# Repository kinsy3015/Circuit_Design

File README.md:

# Circuit_Design

# Internal Oscillatation eqi Circuit

# Wheatstone Current to Voltage

# POWER MANAGEMENT BASIC

# RF class C ( LC Resonant Circuit )

# NE555 안정 / 비안정, 스위칭 레귤레이터, Voltage Divider, Adder(Opamp)

# 다이오드 브릿지 +, -

# ADC IC, MUX/DEMUX

# Gerber

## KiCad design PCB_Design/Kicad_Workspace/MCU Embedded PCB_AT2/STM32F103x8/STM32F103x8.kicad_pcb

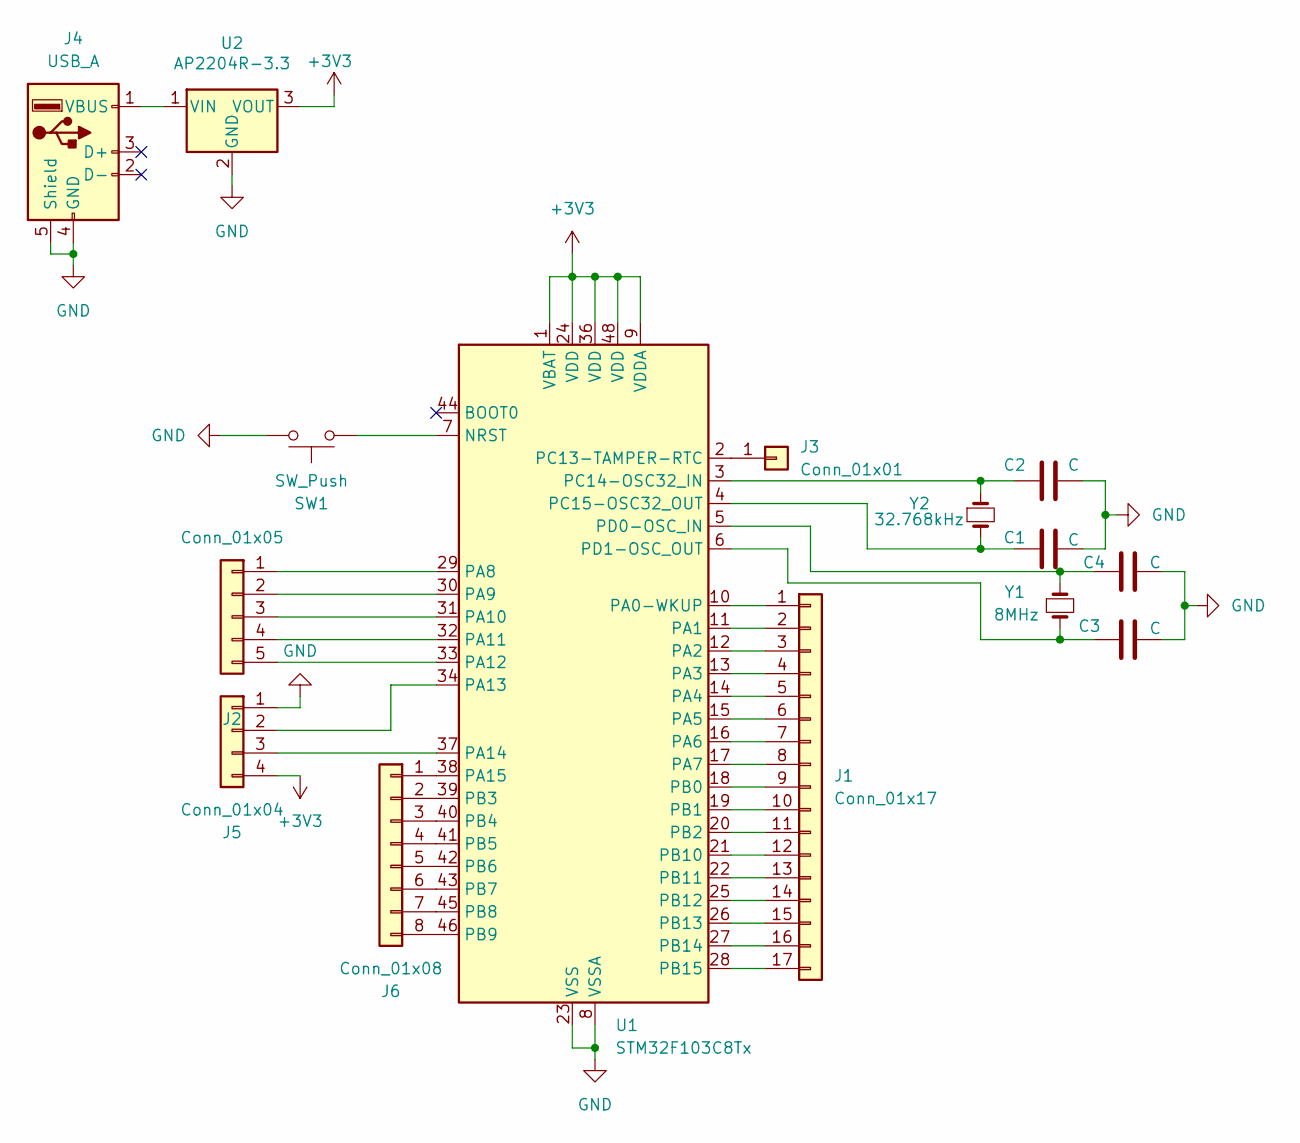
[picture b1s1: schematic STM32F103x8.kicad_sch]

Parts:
C1, C2, C3, C4: C; C_Axial_L3.8mm_D2.6mm_P7.50mm_Horizontal
J1: Conn_01x17; PinHeader_1x17_P2.54mm_Vertical
J2: Conn_01x05; PinHeader_1x05_P2.54mm_Vertical
J3: Conn_01x01; PinHeader_1x01_P2.54mm_Vertical
J4: USB_A; USB_A_Molex_48037-2200_Horizontal
J5: Conn_01x04; PinHeader_1x04_P2.54mm_Vertical
J6: Conn_01x08; PinHeader_1x08_P2.54mm_Vertical
SW1: SW_Push; SW_PUSH_1P1T_6x3.5mm_H4.3_APEM_MJTP1243
U1: STM32F103C8Tx; LQFP-48_7x7mm_P0.5mm
U2: AP2204R-3.3; SOT-89-3
Y1: 8MHz; Crystal_HC49-U_Vertical
Y2: 32.768kHz; Crystal_SMD_Abracon_ABM3-2Pin_5.0x3.2mm

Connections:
+3V3: J5.4, U1.1 (VBAT), U1.9 (VDDA), U1.24 (VDD), U1.36 (VDD), U1.48 (VDD), U2.3 (VOUT)
GND: C1.1, C2.1, C3.1, C4.1, J4.4 (GND), J4.5 (Shield), J5.1, SW1.2, U1.8 (VSSA), U1.23 (VSS), U1.35 (VSS), U1.47 (VSS), U2.2 (GND); also elsewhere on the board
unnamed: J1.1, U1.10 (PA0-WKUP)
unnamed: J1.2, U1.11 (PA1)
unnamed: J1.3, U1.12 (PA2)
unnamed: J1.4, U1.13 (PA3)
unnamed: J1.5, U1.14 (PA4)
unnamed: J1.6, U1.15 (PA5)
unnamed: J1.7, U1.16 (PA6)
unnamed: J1.8, U1.17 (PA7)
unnamed: J1.9, U1.18 (PB0)
unnamed: J1.10, U1.19 (PB1)
unnamed: J1.11, U1.20 (PB2)
unnamed: J1.12, U1.21 (PB10)
unnamed: J1.13, U1.22 (PB11)
unnamed: J1.14, U1.25 (PB12)
unnamed: J1.15, U1.26 (PB13)
unnamed: J1.16, U1.27 (PB14)
unnamed: J1.17, U1.28 (PB15)
unnamed: J2.1, U1.29 (PA8)
unnamed: J2.2, U1.30 (PA9)
unnamed: J2.3, U1.31 (PA10)
unnamed: J2.4, U1.32 (PA11)
unnamed: J2.5, U1.33 (PA12)
unnamed: J3.1, U1.2 (PC13-TAMPER-RTC)
unnamed: J4.1 (VBUS), U2.1 (VIN)
unnamed: J5.2, U1.34 (PA13)
unnamed: J5.3, U1.37 (PA14)
unnamed: J6.1, U1.38 (PA15)
unnamed: J6.2, U1.39 (PB3)
unnamed: J6.3, U1.40 (PB4)
unnamed: J6.4, U1.41 (PB5)
unnamed: J6.5, U1.42 (PB6)
unnamed: J6.6, U1.43 (PB7)
unnamed: J6.7, U1.45 (PB8)
unnamed: J6.8, U1.46 (PB9)
unnamed 36: SW1.1, U1.7 (NRST); also elsewhere on the board
unnamed: C2.2, U1.3 (PC14-OSC32_IN), Y2.1
unnamed: C1.2, U1.4 (PC15-OSC32_OUT), Y2.2
unnamed: C4.2, U1.5 (PD0-OSC_IN), Y1.1
unnamed: C3.2, U1.6 (PD1-OSC_OUT), Y1.2

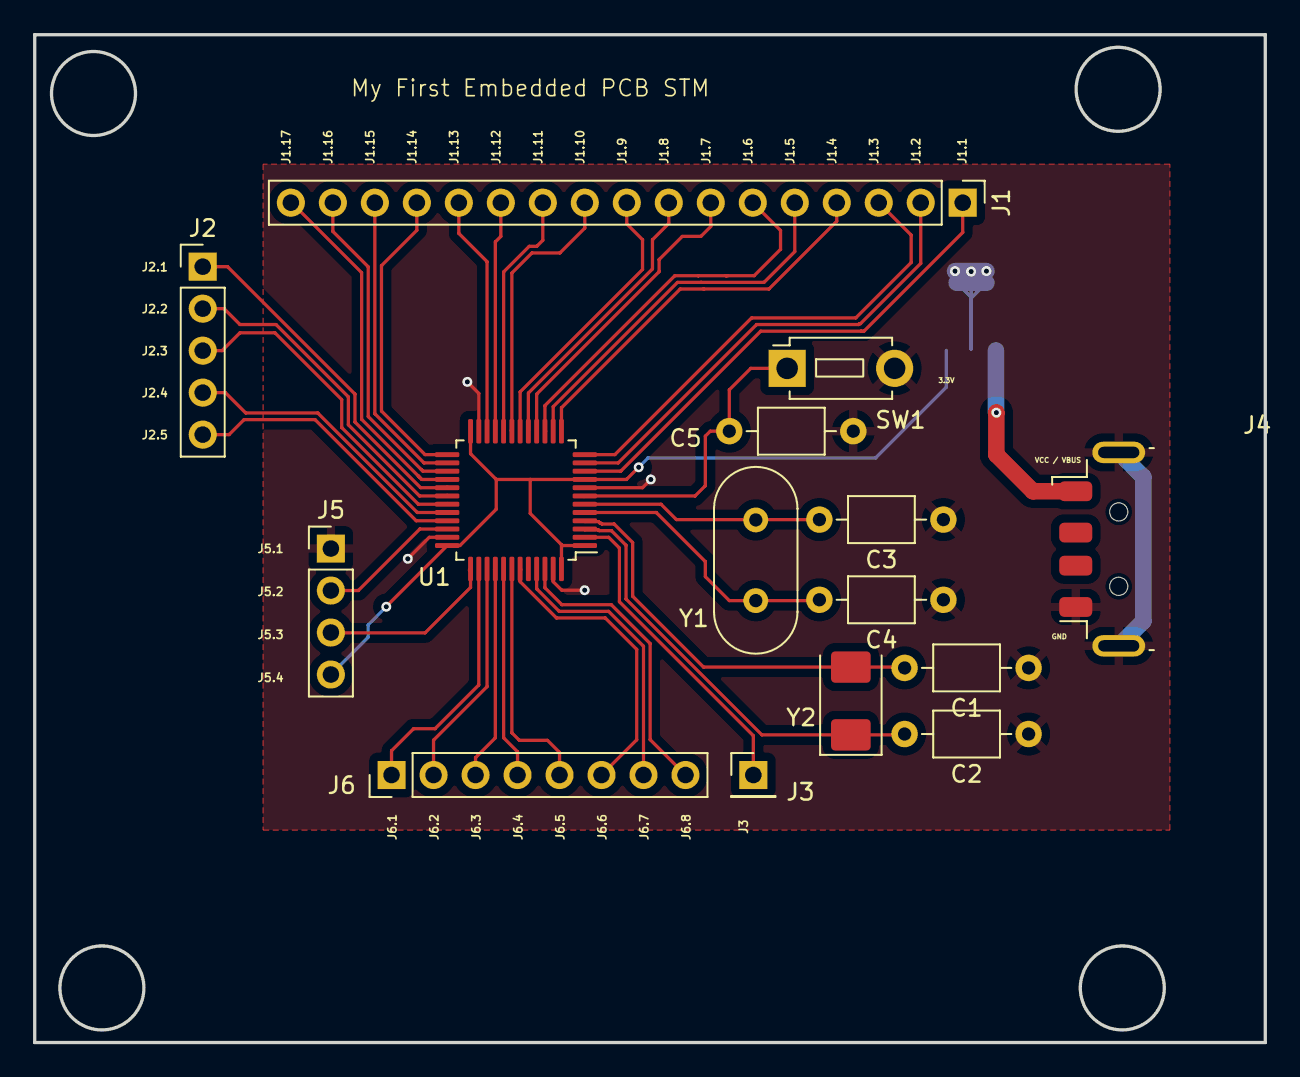
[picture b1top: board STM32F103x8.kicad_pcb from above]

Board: 2 copper layers, 74.4 x 61.0 mm, 16 parts (1 on the bottom side), 41 nets.

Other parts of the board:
C5: C; C_Axial_L3.8mm_D2.6mm_P7.50mm_Horizontal

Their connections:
GND: C5.2; also elsewhere on the board
unnamed 36: C5.1; also elsewhere on the board

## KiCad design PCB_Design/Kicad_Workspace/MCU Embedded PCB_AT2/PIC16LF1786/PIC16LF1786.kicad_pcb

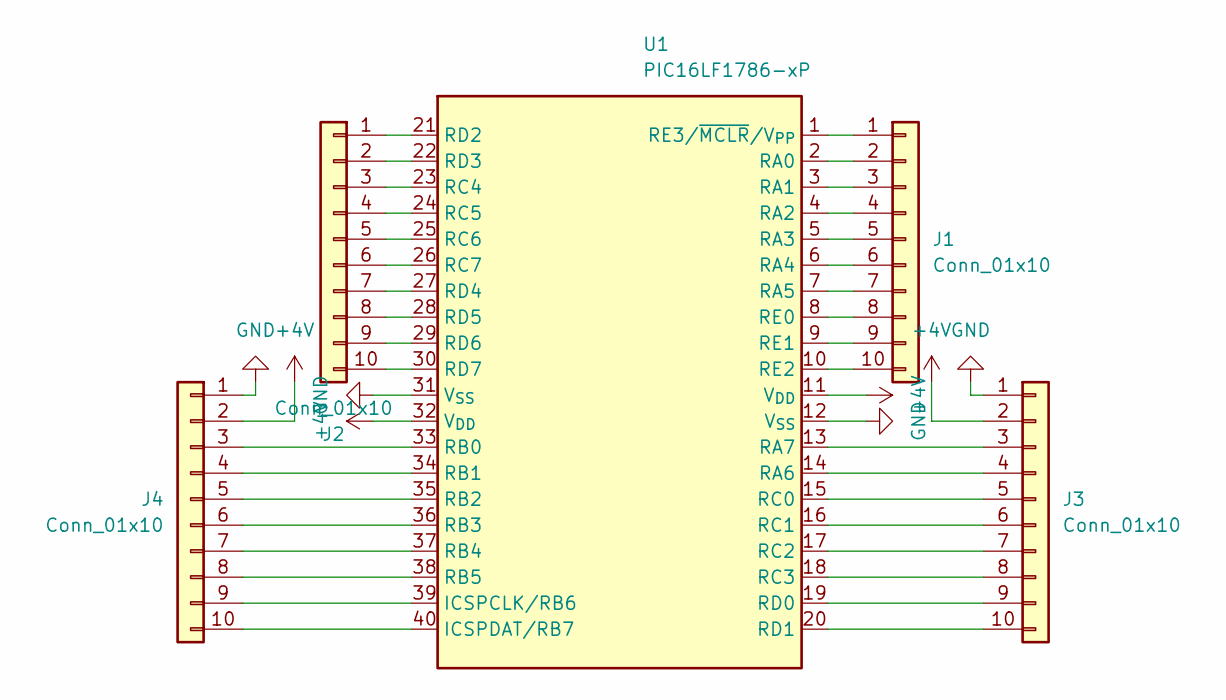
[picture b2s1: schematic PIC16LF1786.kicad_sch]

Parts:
J1, J2, J3, J4: Conn_01x10; PinHeader_1x10_P2.54mm_Vertical
U1: PIC16LF1786-xP; DIP-40_W15.24mm

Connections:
+4V: J3.2, J4.2, U1.11 (V_{DD}), U1.32 (V_{DD})
GND: J3.1, J4.1, U1.12 (V_{SS}), U1.31 (V_{SS})
unnamed: J1.1, U1.1 (RE3/~MCLR/V_{PP})
unnamed: J1.2, U1.2 (RA0)
unnamed: J1.3, U1.3 (RA1)
unnamed: J1.4, U1.4 (RA2)
unnamed: J1.5, U1.5 (RA3)
unnamed: J1.6, U1.6 (RA4)
unnamed: J1.7, U1.7 (RA5)
unnamed: J1.8, U1.8 (RE0)
unnamed: J1.9, U1.9 (RE1)
unnamed: J1.10, U1.10 (RE2)
unnamed: J2.1, U1.21 (RD2)
unnamed: J2.2, U1.22 (RD3)
unnamed: J2.3, U1.23 (RC4)
unnamed: J2.4, U1.24 (RC5)
unnamed: J2.5, U1.25 (RC6)
unnamed: J2.6, U1.26 (RC7)
unnamed: J2.7, U1.27 (RD4)
unnamed: J2.8, U1.28 (RD5)
unnamed: J2.9, U1.29 (RD6)
unnamed: J2.10, U1.30 (RD7)
unnamed: J3.3, U1.13 (RA7)
unnamed: J3.4, U1.14 (RA6)
unnamed: J3.5, U1.15 (RC0)
unnamed: J3.6, U1.16 (RC1)
unnamed: J3.7, U1.17 (RC2)
unnamed: J3.8, U1.18 (RC3)
unnamed: J3.9, U1.19 (RD0)
unnamed: J3.10, U1.20 (RD1)
unnamed: J4.3, U1.33 (RB0)
unnamed: J4.4, U1.34 (RB1)
unnamed: J4.5, U1.35 (RB2)
unnamed: J4.6, U1.36 (RB3)
unnamed: J4.7, U1.37 (RB4)
unnamed: J4.8, U1.38 (RB5)
unnamed: J4.9, U1.39 (ICSPCLK/RB6)
unnamed: J4.10, U1.40 (ICSPDAT/RB7)

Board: 2 copper layers, 5 parts (0 on the bottom side), 38 nets, no tracks yet.

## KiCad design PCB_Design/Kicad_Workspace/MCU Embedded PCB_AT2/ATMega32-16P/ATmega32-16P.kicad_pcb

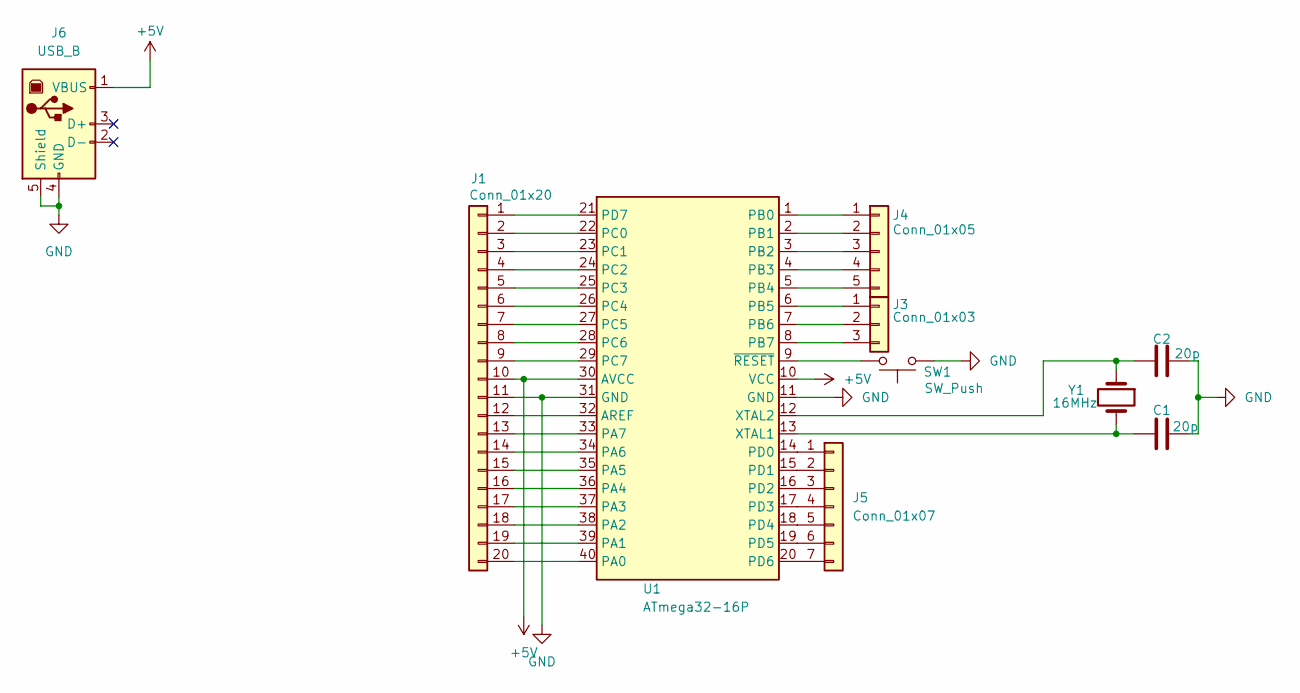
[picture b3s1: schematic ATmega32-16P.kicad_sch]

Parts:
C1, C2: 20p; C_Axial_L3.8mm_D2.6mm_P7.50mm_Horizontal
J1: Conn_01x20; PinHeader_1x20_P2.54mm_Vertical
J3: Conn_01x03; PinHeader_1x03_P2.54mm_Vertical
J4: Conn_01x05; PinHeader_1x05_P2.54mm_Vertical
J5: Conn_01x07; PinHeader_1x07_P2.54mm_Vertical
J6: USB_B; USB_B_OST_USB-B1HSxx_Horizontal
SW1: SW_Push; SW_DIP_SPSTx01_Slide_6.7x4.1mm_W8.61mm_P2.54mm_LowProfile
U1: ATmega32-16P; DIP-40_W15.24mm
Y1: 16MHz; Crystal_HC49-U_Vertical

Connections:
+5V: J1.10, J6.1 (VBUS), U1.10 (VCC), U1.30 (AVCC)
GND: C1.1, C2.1, J1.11, J6.4 (GND), J6.5 (Shield), SW1.1, U1.11 (GND), U1.31 (GND)
unnamed: J1.1, U1.21 (PD7)
unnamed: J1.2, U1.22 (PC0)
unnamed: J1.3, U1.23 (PC1)
unnamed: J1.4, U1.24 (PC2)
unnamed: J1.5, U1.25 (PC3)
unnamed: J1.6, U1.26 (PC4)
unnamed: J1.7, U1.27 (PC5)
unnamed: J1.8, U1.28 (PC6)
unnamed: J1.9, U1.29 (PC7)
unnamed: J1.12, U1.32 (AREF)
unnamed: J1.13, U1.33 (PA7)
unnamed: J1.14, U1.34 (PA6)
unnamed: J1.15, U1.35 (PA5)
unnamed: J1.16, U1.36 (PA4)
unnamed: J1.17, U1.37 (PA3)
unnamed: J1.18, U1.38 (PA2)
unnamed: J1.19, U1.39 (PA1)
unnamed: J1.20, U1.40 (PA0)
unnamed: J3.1, U1.6 (PB5)
unnamed: J3.2, U1.7 (PB6)
unnamed: J3.3, U1.8 (PB7)
unnamed: J4.1, U1.1 (PB0)
unnamed: J4.2, U1.2 (PB1)
unnamed: J4.3, U1.3 (PB2)
unnamed: J4.4, U1.4 (PB3)
unnamed: J4.5, U1.5 (PB4)
unnamed: J5.1, U1.14 (PD0)
unnamed: J5.2, U1.15 (PD1)
unnamed: J5.3, U1.16 (PD2)
unnamed: J5.4, U1.17 (PD3)
unnamed: J5.5, U1.18 (PD4)
unnamed: J5.6, U1.19 (PD5)
unnamed: J5.7, U1.20 (PD6)
unnamed: C1.2, U1.13 (XTAL1), Y1.2
unnamed: C2.2, U1.12 (XTAL2), Y1.1
unnamed: SW1.2, U1.9 (~RESET)

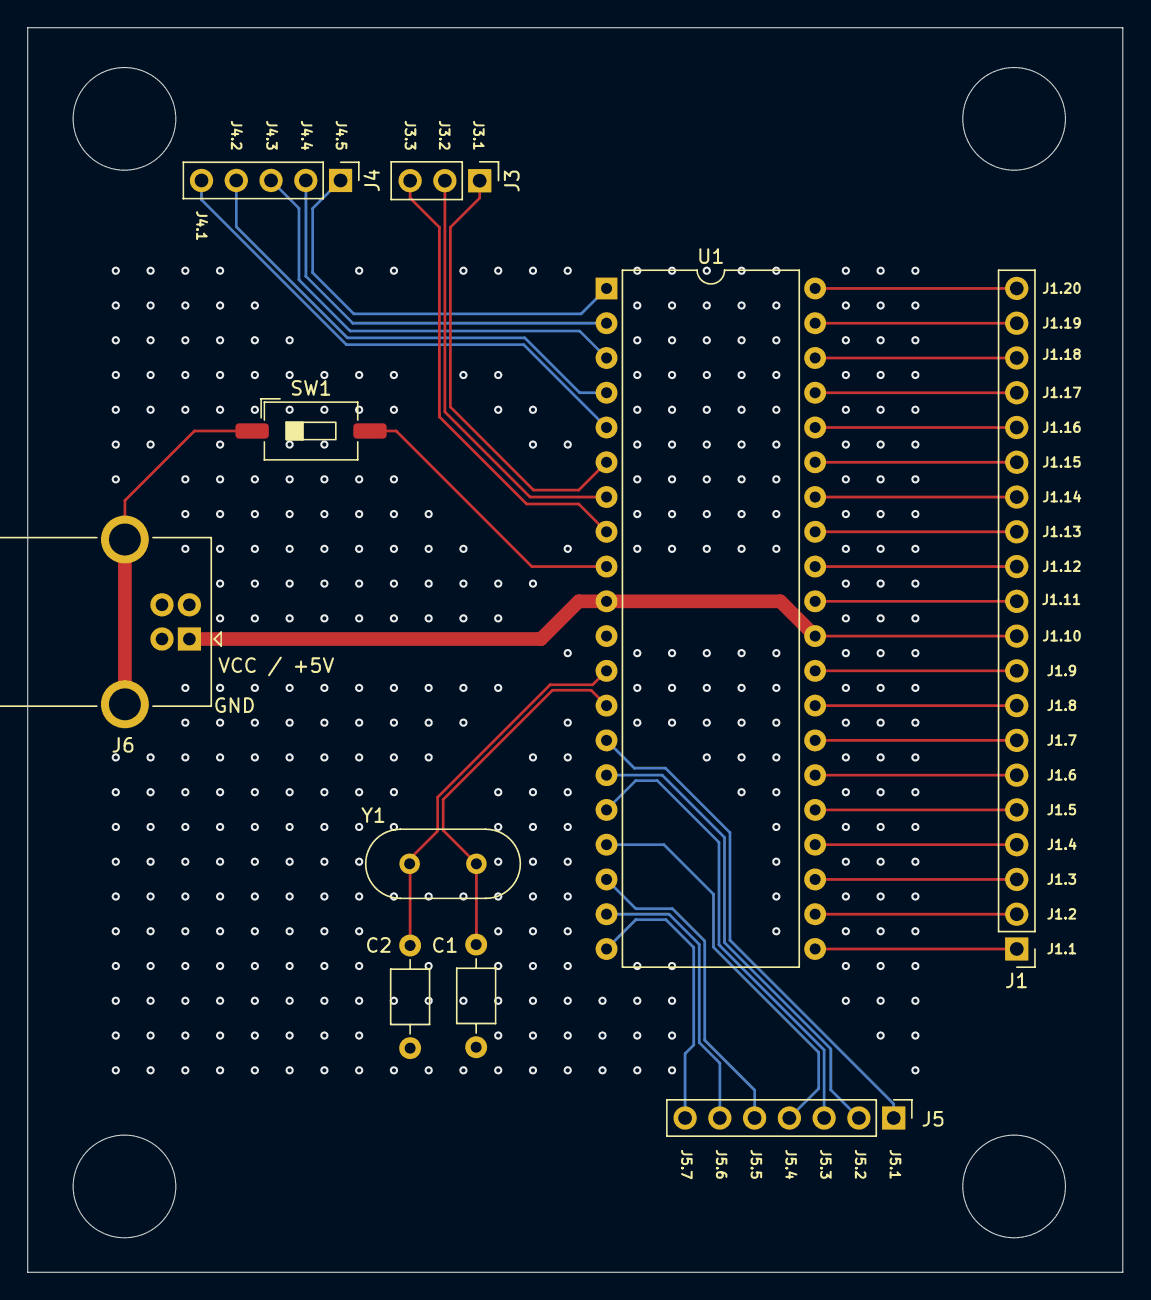
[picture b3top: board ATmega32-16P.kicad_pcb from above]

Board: 2 copper layers, 80.0 x 90.9 mm, 10 parts (0 on the bottom side), 38 nets.

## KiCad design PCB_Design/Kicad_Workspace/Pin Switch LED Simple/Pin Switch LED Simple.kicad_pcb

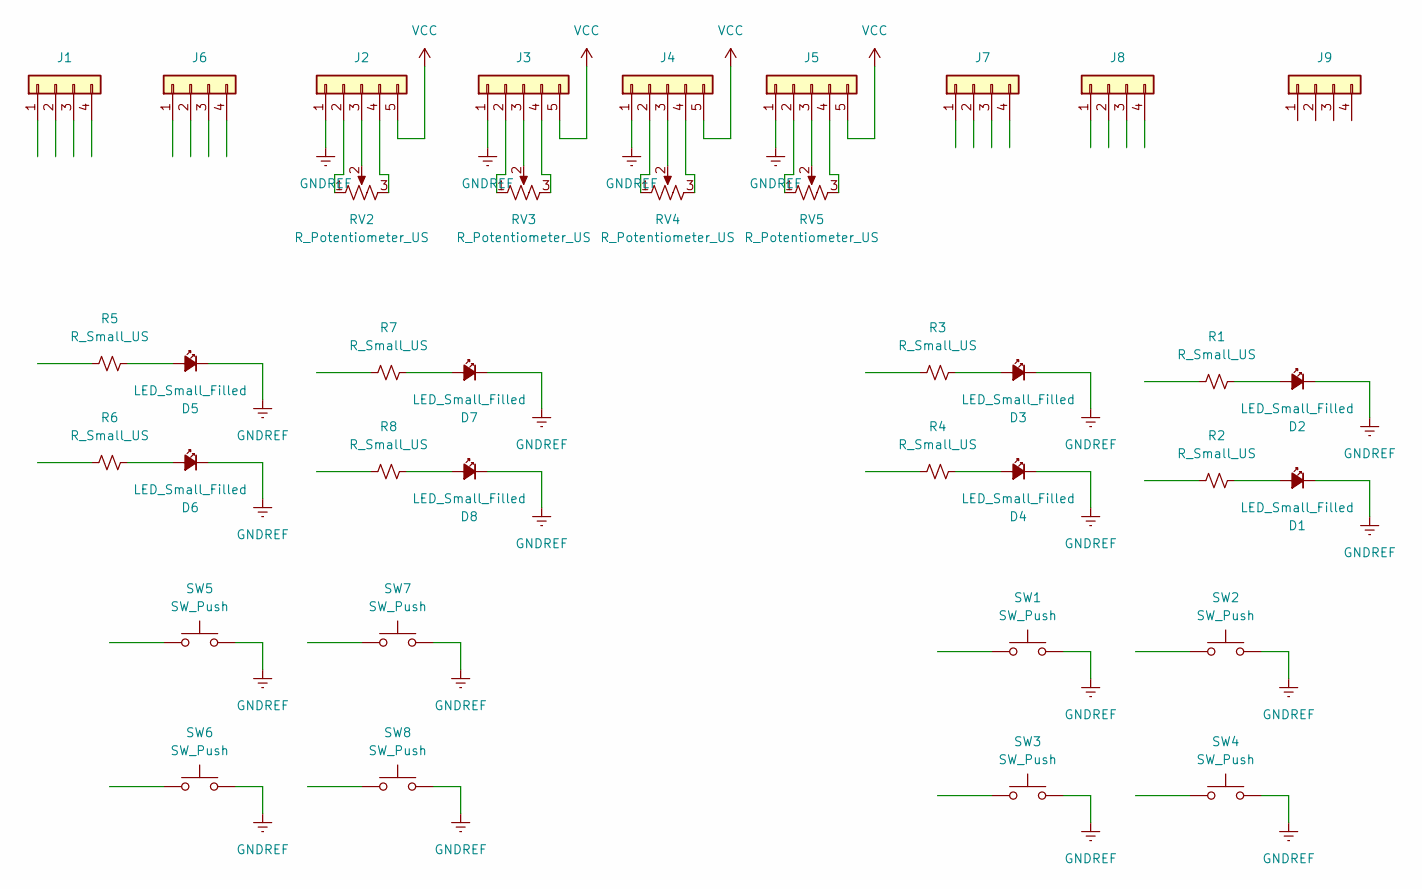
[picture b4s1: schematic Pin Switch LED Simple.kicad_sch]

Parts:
D1, D2, D3, D4, D5, D6, D7, D8: LED_Small_Filled; LED_D5.0mm
J1, J6, J7, J8, J9: Conn_01x04; PinHeader_1x04_P2.54mm_Vertical
J2, J3, J4, J5: Conn_01x05; PinHeader_1x05_P2.54mm_Vertical
R1, R2, R3, R4, R5, R6, R7, R8: R_Small_US; R_Axial_DIN0207_L6.3mm_D2.5mm_P10.16mm_Horizontal
RV2, RV3, RV4, RV5: R_Potentiometer_US; Potentiometer_Vishay_T73XW_Horizontal
SW1, SW2, SW3, SW4, SW5, SW6, SW7, SW8: SW_Push; SW_PUSH-12mm

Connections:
GNDREF: D1.1 (K), D2.1 (K), D3.1 (K), D4.1 (K), D5.1 (K), D6.1 (K), D7.1 (K), D8.1 (K), J2.1, J3.1, J4.1, J5.1, SW1.2, SW2.2, SW3.2, SW4.2, SW5.2, SW6.2, SW7.2, SW8.2
unnamed: D1.2 (A), R2.2
unnamed: D2.2 (A), R1.2
unnamed: D3.2 (A), R3.2
unnamed: D4.2 (A), R4.2
unnamed: D5.2 (A), R5.2
unnamed: D6.2 (A), R6.2
unnamed: D7.2 (A), R7.2
unnamed: D8.2 (A), R8.2
unnamed: J2.2, RV2.1
unnamed: J2.3, RV2.2
unnamed: J2.4, RV2.3
unnamed: J3.2, RV3.1
unnamed: J3.3, RV3.2
unnamed: J3.4, RV3.3
unnamed: J4.2, RV4.1
unnamed: J4.3, RV4.2
unnamed: J4.4, RV4.3
unnamed: J5.2, RV5.1
unnamed: J5.3, RV5.2
unnamed: J5.4, RV5.3
VCC: J2.5, J3.5, J4.5, J5.5

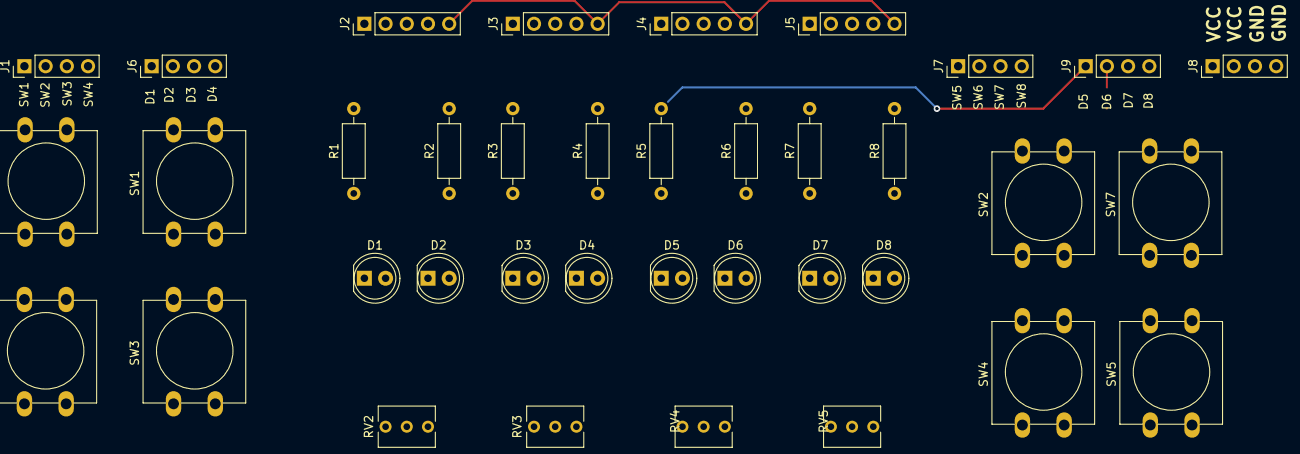
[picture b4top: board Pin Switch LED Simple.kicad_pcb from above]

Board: 2 copper layers, 37 parts (0 on the bottom side), 22 nets.

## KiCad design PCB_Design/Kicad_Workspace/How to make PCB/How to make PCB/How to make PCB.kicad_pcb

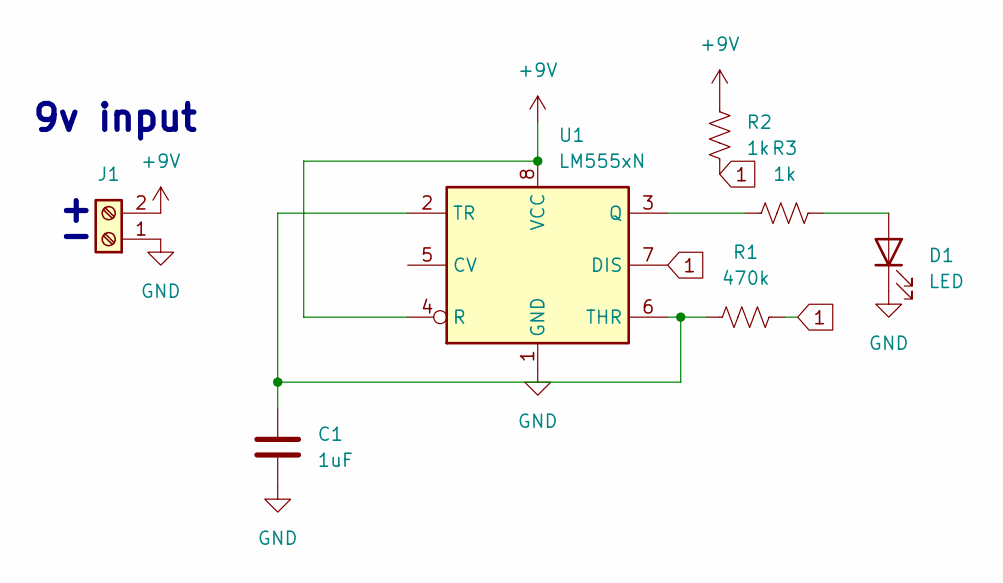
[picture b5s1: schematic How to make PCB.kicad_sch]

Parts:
C1: 1uF; C_Disc_D5.0mm_W2.5mm_P2.50mm
D1: LED; LED_D5.0mm
J1: Screw_Terminal_01x02; TerminalBlock_bornier-2_P5.08mm
R1: 470k; R_Axial_DIN0207_L6.3mm_D2.5mm_P10.16mm_Horizontal
R2, R3: 1k; R_Axial_DIN0207_L6.3mm_D2.5mm_P10.16mm_Horizontal
U1: LM555xN; DIP-8_W7.62mm_LongPads

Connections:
1: R1.2, R2.2, U1.7 (DIS)
+9V: J1.2, R2.1, U1.4 (R), U1.8 (VCC)
GND: C1.2, D1.1 (K), J1.1, U1.1 (GND)
unnamed: D1.2 (A), R3.2
unnamed: R3.1, U1.3 (Q)
unnamed: C1.1, R1.1, U1.2 (TR), U1.6 (THR)

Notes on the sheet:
9v input

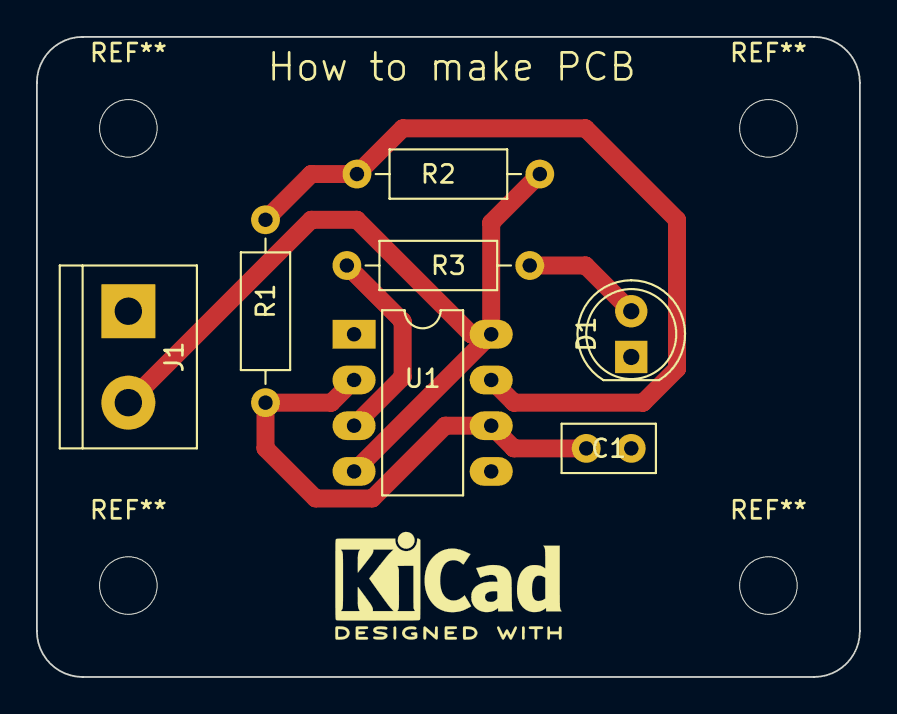
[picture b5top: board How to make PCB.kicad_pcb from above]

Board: 2 copper layers, 45.7 x 35.6 mm, 7 parts (0 on the bottom side), 6 nets.

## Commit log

2024-10-08 update_prj
2024-10-11 MCU_Top_Design
2024-10-22 updatePCBHDLVLSI
2024-10-24 update_PADS
2025-06-19 update_gerber
2025-06-19 update_stm
